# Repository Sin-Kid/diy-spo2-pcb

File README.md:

# DIY SpO2 PCB

A two-layer through-hole PCB for a DIY pulse oximeter, designed in KiCad 10. An Arduino Nano reads a MAX30102 sensor module and drives an SSD1306 display.

## 3D view

The Arduino Nano, OLED display and MAX30102 module have no 3D models here, so they appear only as outlines.

## PCB layout

## Schematic

## Parts

| Ref | Part |
| --- | --- |
| A1 | Arduino Nano v3.x |
| U1 | SSD1306 display module |
| U2 | MAX30102 sensor module |
| SW1–SW3 | 6 mm push buttons |
| D1 | 3 mm LED |
| R1–R4 | 1k resistors |
| C1–C3 | 100n capacitors |

## Files

- `proj-1.kicad_pro`, `.kicad_sch`, `.kicad_pcb`: the KiCad project. Open the `.kicad_pro` file in KiCad.
- `spo2_stuff.pretty/`: custom footprints for the MAX30102 and SSD1306 modules.
- `images/`: screenshots of the PCB layout, 3D view and schematic.
- `gerbers/`: fabrication files. `diysp02v1_gerbers.zip` is ready to upload to a PCB manufacturer.

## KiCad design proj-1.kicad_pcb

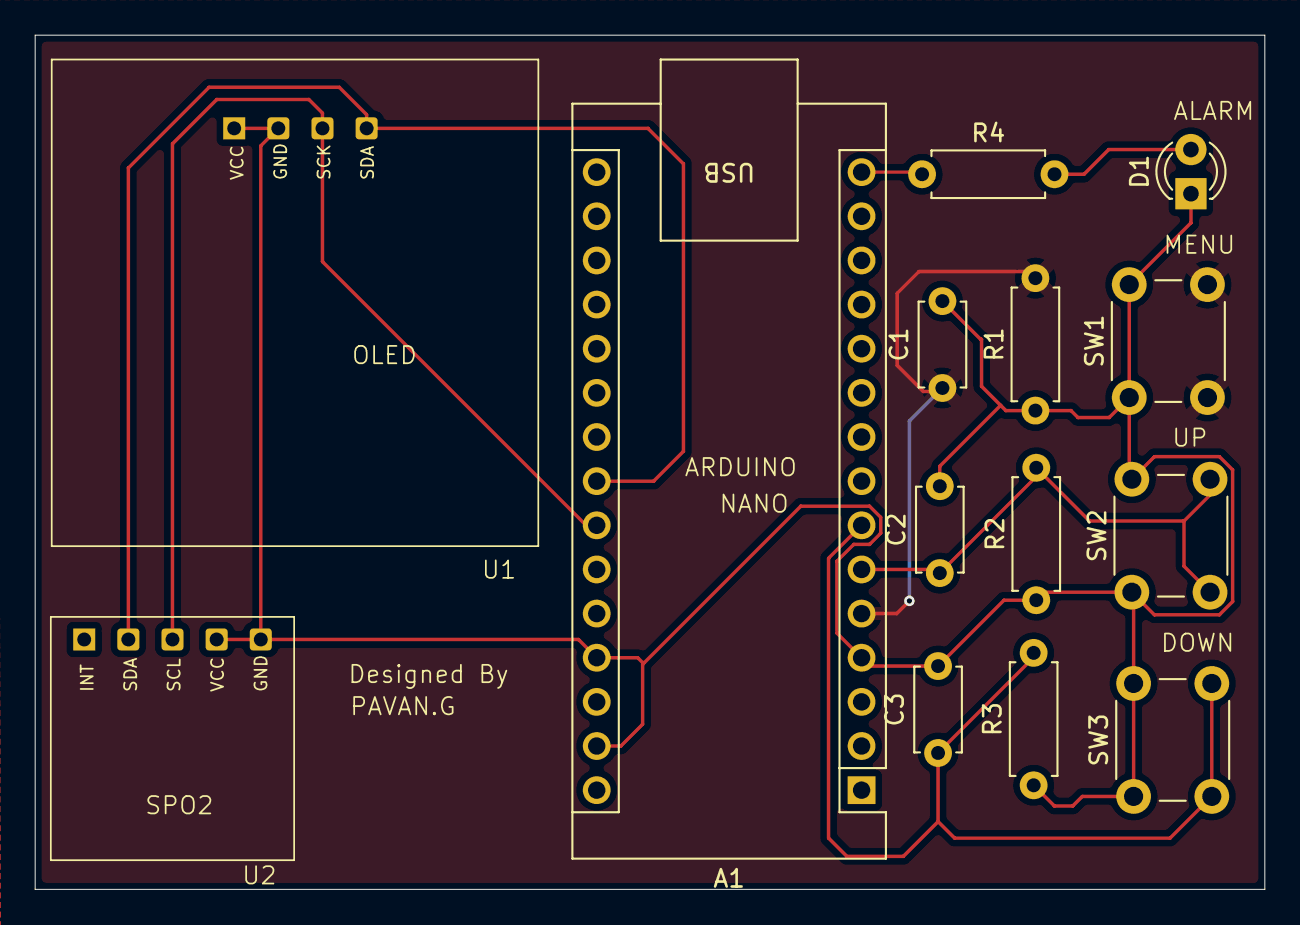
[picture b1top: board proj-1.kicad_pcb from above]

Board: 2 copper layers, 70.8 x 49.1 mm, 14 parts (0 on the bottom side), 8 nets.

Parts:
A1: Arduino_Nano_v3.x; Arduino_Nano
C1, C2, C3: 100n; C_Disc_D4.7mm_W2.5mm_P5.00mm
D1: LED; LED_D3.0mm
R1, R2, R3, R4: 1k; R_Axial_DIN0207_L6.3mm_D2.5mm_P7.62mm_Horizontal
SW1, SW2, SW3: SW_Push; SW_PUSH_6mm
U1: SSD1306
U2: MAX30102; MAX30102_Module

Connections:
+5V: A1.4 (GND), A1.27 (+5V), A1.29 (GND), C1.2, C2.2, C3.2, D1.1 (K), R1.1, R2.1, R3.1, SW1.1, SW2.1, SW3.1, U1.1 (GND), U1.2 (VCC), U2.4 (GND), U2.5 (VCC)
unnamed: A1.5 (D2), C1.1, R1.2, SW1.2
unnamed: A1.6 (D3), C2.1, R2.2, SW2.2
unnamed: A1.7 (D4), C3.1, R3.2, SW3.2
unnamed: A1.15 (D12), R4.1
unnamed: D1.2 (A), R4.2
unnamed: A1.24 (A5), U1.3 (SCL), U2.3 (SCL)
unnamed: A1.23 (A4), U1.4 (SDA), U2.2 (SDA)
